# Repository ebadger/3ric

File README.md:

<h1 align="center">3ric</h1>

<p align="center">
  <strong>A from-scratch, Apple-II-class 65C02 personal computer — real hardware plus a
  cycle-honest emulator that also runs in your browser.</strong>
</p>

<p align="center">

</p>

---

## ▶ Try it now — no install, no account

**[Built from Bits: the Hackaday showcase](https://ebadger.github.io/3ric/hackaday.html)**
is a one-minute tour of the machine: a hi-res starfield, 16-color plasma, a rotating
wireframe, and an original six-voice stereo chiptune, all running as real 65C02 code.
[Run and remix the demo](https://ebadger.github.io/3ric/index.html?src=programs/hackaday.s)
at **1x**, then click the emulator for sound. Use **1-4** for scenes, **Space** to pause,
**M** to mute, and **Q/Esc** to return to the monitor. Source and `.PRG` / `.woz`
exports are available in the editor; the program targets 3RIC, not an unmodified Apple II.

**<https://ebadger.github.io/3ric/>** runs the *entire machine* client-side via
WebAssembly. Click the canvas and start typing at the DOS `>` prompt (`MON` enters the
monitor's `*` prompt). Then:

- **Boot Disk** — boot the demo 5.25″ floppy (a self-booting machine-code disk).
- **Mount SD** — mount the micro-SD card and use the ROM's DOS shell (`DIR`, etc.).
- **Play Dirt Bike** — [ebadger.github.io/3ric/?brun=DIRTBIKE/DIRTBIKE.PRG](https://ebadger.github.io/3ric/?brun=DIRTBIKE/DIRTBIKE.PRG)
  boots Arnaud Verhille's Apple II motocross from the SD card through the ROM DOS
  (`CD DIRTBIKE`, `BRUN DIRTBIKE.PRG 0800`). It takes about 10 seconds to load; play
  with the keyboard or a gamepad.
- **Assemble & Run** — open the built-in 65C02 editor, write assembly, and run it like
  `BRUN` — all in the browser. Programs are shareable via a `?src=` deep link.

<!-- TODO(media): drop an animated GIF of the emulator booting + a program running here,
     e.g. . Keep it < ~5 MB for fast README loads. -->

## What is 3ric?

3ric is a personal *learn-by-building* project: an 8-bit computer designed at the chip level
— KiCad schematics, a custom PCB, and 74-series address-decode logic — paired with a C++
emulator of the exact same machine. The emulator compiles to WebAssembly, so the **same VM
core** that models the real hardware also boots the unmodified 512 KB ROM in any browser.
The whole journey is documented in a [YouTube build series][youtube].

> **Why it exists:** to understand, build, document, and demonstrate how an Apple-II-class
> computer works end to end — and to let anyone poke at it with zero friction. See
> [`docs/MISSION.md`](docs/MISSION.md).

## Features

- **65C02 CPU** with a faithful memory map and soft switches, adjustable clock speed.
- **Video**: 40×24 text, lo-res, and hi-res color, rendered to a canvas.
- **Input & I/O**: keyboard (`$C000`/`$C010`), 6551-style ACIA serial, 6522 VIA.
- **Disk II 5.25″ floppy** via `.woz` images (self-booting machine-code disks).
- **Micro-SD storage**: a bit-banged SPI FAT32 card with a ROM DOS shell.
- **In-browser 65C02 assembler/editor** — assemble & run, download a `.PRG`, share `?src=`
  links; ships ~11 sample programs.
- **AI-generated 6502 games** (STAR DUEL, Snake, Life, Minesweeper, 2048, Star Swarm, and more) built
  through the project's own codegen pipeline — see [`emulator/AICodeGen/`](emulator/AICodeGen/).
- **Runs everywhere the same way**: one shared C++ VM core drives both the native Windows
  build and the browser (WebAssembly) build.

## Write your first program in the browser

1. Open the [live emulator][demo] and pick a sample from the editor's program menu.
2. Edit the assembly, hit **Assemble & Run**, and watch it execute on the machine.
3. Use **Download .PRG** to save it, or copy the `?src=` link to share the exact program.

Prebuilt samples live in [`web/programs/`](web/programs/); their source and design notes
are under [`emulator/AICodeGen/`](emulator/AICodeGen/) and [`codegen/`](codegen/).

## Build from source

Full, current instructions are in [`status/SYSTEM-STATUS.md`](status/SYSTEM-STATUS.md).

**Native emulator (Windows):** open `emulator/Badger6502VM.sln` in Visual Studio 2022 and
build/run the `Console` or WinUI (`Badger6502Emulator`) host.

**Browser / WebAssembly build** (emsdk 6.0.1, Node, Python 3):

```powershell
pwsh web/build.ps1     # Emscripten -> web/badger6502.js + .wasm, stages data/
pwsh web/serve.ps1     # serves http://localhost:8011/index.html
```

**Verify it's healthy** (headless smoke tests — no WASM build needed for the first one):

```powershell
$node = "C:\Users\ebadger\emsdk\node\22.16.0_64bit\bin\node.exe"
& $node codegen/tools/asm6502.test.mjs   # assembler encoding tests
& $node web/test_boot.cjs                # ROM boots to a sane state
```

## How it works

```mermaid
flowchart TD
    ROM["6502 ROM + software<br/>(badger6502.bin, fontrom.dat, .s / .prg)"]
    VM["Emulator core — 65C02 VM in C++<br/>(WozLib floppy · MockMicroSD · video/keyboard/ACIA/VIA)"]
    NATIVE["Native hosts<br/>(Windows / Console)"]
    WASM["Emscripten bridge → WebAssembly"]
    BROWSER["Browser client (index.html)<br/>→ GitHub Pages"]
    CODEGEN["Codegen<br/>(asm6502 + headless harness)"]
    HW["Hardware<br/>(KiCad · 74-series logic · logisim)"]

    ROM --> VM
    VM --> NATIVE
    VM --> WASM --> BROWSER
    CODEGEN -->|assembles & tests on the same VM| VM
    HW -. mirrors the same memory map .-> VM
```

The **memory map is a shared contract**: `emulator/Badger6502VMLib/vm.h` is mirrored by the
hardware decode schematic, the web bridge, and the codegen platform reference. The architecture and
each layer are documented in [`specs/`](specs/) — start with
[`specs/SYSTEM.md`](specs/SYSTEM.md).

## Repository layout

| Path | What's there |
|------|--------------|
| [`emulator/`](emulator/) | C++ 65C02 VM core, WozLib, MockMicroSD, native hosts, ROM data, AI codegen programs |
| [`web/`](web/) | Emscripten bridge, browser client, in-browser assembler, Pages build/deploy |
| [`codegen/`](codegen/) | `asm6502` assembler, `run6502`/harness, platform-ref generation |
| [`specs/`](specs/) | Layer specifications (the source of truth — specs before code) |
| [`status/`](status/) | How to build/run/verify; current state and known gaps |
| [`docs/`](docs/) | Mission, workflow rules & learnings, roles |
| [`kicad/`](kicad/), [`logisim/`](logisim/), [`diylayout/`](diylayout/), [`schematic_pdf/`](schematic_pdf/) | Hardware: schematics, PCB, 74-series address decode, digital-logic models |
| [`22v10/`](22v10/) | Historical intermediate GAL experiments; replaced by 74-series logic in the final build |
| [`romgen/`](romgen/), [`scripts/`](scripts/), [`test/`](test/) | ROM assembly tooling, dev/CI scripts, tests |

## Known gaps

- **DOS 3.3 / Applesoft disks don't run.** This clone's `$E000` BASIC is generic Microsoft
  BASIC, not Applesoft, so games that chain through an Applesoft auto-run greeting won't
  boot. Self-booting machine-code disks work.

## Contributing

Contributions and experiments are welcome — especially new 6502 programs for the gallery.

**Add a program (the easy path).** No C++, no local build: have an AI coding tool write a
65C02 program by pointing it at [`llms.txt`](https://ebadger.github.io/3ric/llms.txt), test it
in the [browser editor][demo], and open a one-file pull request to the
[Community Gallery](https://ebadger.github.io/3ric/gallery.html). Step-by-step, with a
copy-paste prompt: **[`CONTRIBUTING.md`](CONTRIBUTING.md)**.

**Change the machine itself.** A few house rules keep it trustworthy:

- **Specs before code.** Update the relevant spec in [`specs/`](specs/) in the same change.
- **Trace every layer** a change touches (ROM/software → C++ VM core → web bridge/WASM), and
  keep the **native and browser builds behavior-identical**.
- **Open a PR** — changes land via pull request, not direct pushes to `main`.

The full workflow rules live in [`docs/LEARNINGS.md`](docs/LEARNINGS.md); bug reports use the
templates under [`.github/ISSUE_TEMPLATE/`](.github/ISSUE_TEMPLATE/).

## The build series

3ric is built in public. Watch the design and construction, episode by episode:
**[YouTube build series][youtube]**.

The [porting logs](docs/porting-logs/README.md) tell the software side of that story:
A2Robots, Spy vs Spy, Spy Hunter, and Pitfall II, with the changes, failed experiments,
hardware evidence, and lessons for future sessions.

## Support

If this project helps you learn or you just enjoy the build, please consider
**[sponsoring it on GitHub][sponsor]** — or use the **Sponsor** button at the top of this
repository (see [`.github/FUNDING.yml`](.github/FUNDING.yml)). Sponsorship funds parts,
boards, and more build videos, and **every sponsor is credited in
[`BACKERS.md`](BACKERS.md)**.

## License

3ric is **dual-licensed**:

- **Software** — [MIT](LICENSE).
- **Hardware designs & documentation** — [Creative Commons Attribution-ShareAlike 4.0
  International](LICENSE-CC-BY-SA-4.0.txt).

Bundled third-party components keep their own licenses, and some bundled data (the ROM's
Microsoft BASIC, Apple II disk images used as test fixtures) is third-party copyrighted
material **not** licensed by this project. The emulators' micro-SD card holds **Dirt Bike**,
a separate game under the GNU GPL v3, modified for 3RIC (see
[`emulator/Data/sd-card/`](emulator/Data/sd-card/README.md)). See [`NOTICE`](NOTICE) for the
full breakdown before redistributing.

[demo]: https://ebadger.github.io/3ric/
[youtube]: https://www.youtube.com/playlist?list=PLbYLt1iawSBLK4w46Kn7cxxuoeVt7Zepq
[sponsor]: https://github.com/sponsors/ebadger

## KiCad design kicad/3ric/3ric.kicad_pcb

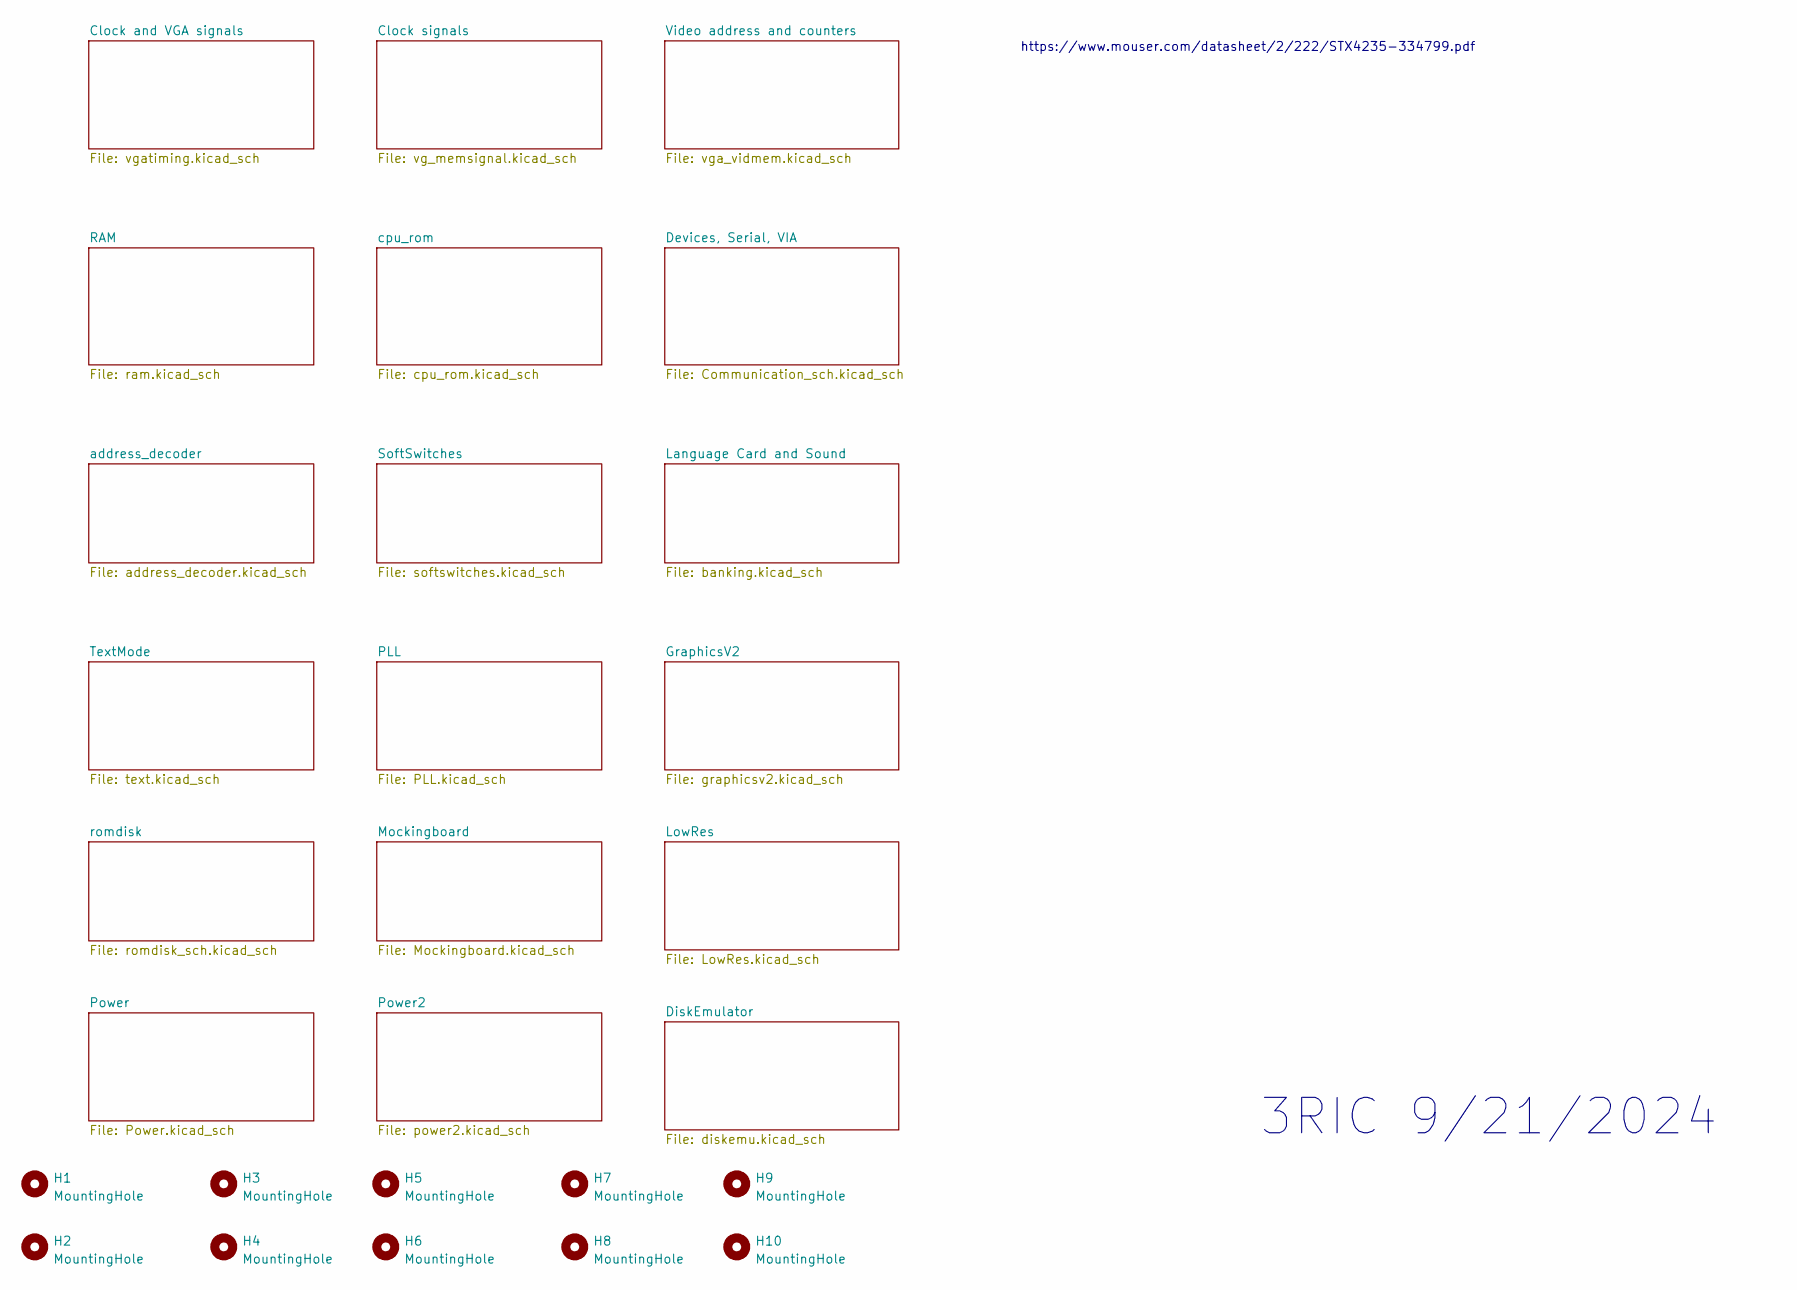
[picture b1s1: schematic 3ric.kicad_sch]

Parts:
H1, H2, H3, H4, H5, H6, H7, H8, H9, H10: MountingHole; MountingHole_4.3mm_M4

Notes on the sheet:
3RIC 9/21/2024
https://www.mouser.com/datasheet/2/222/STX4235-334799.pdf

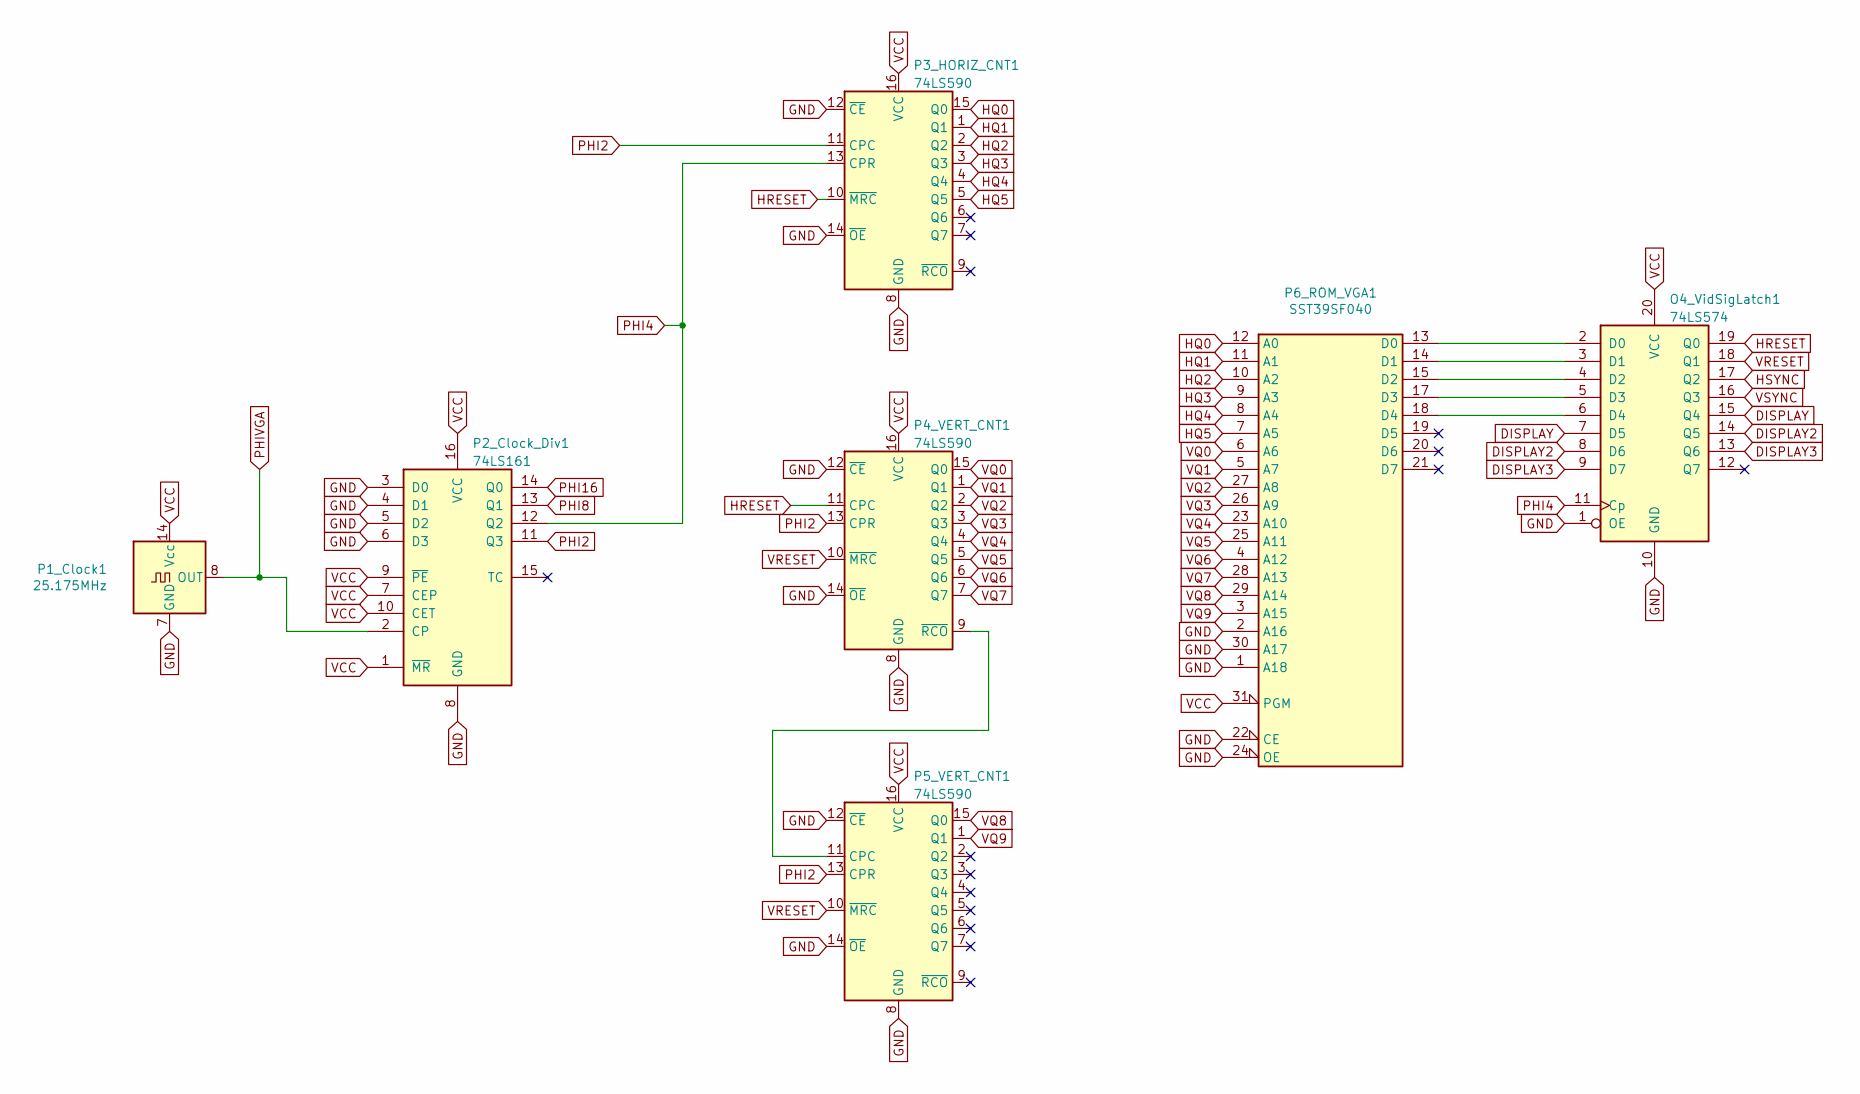
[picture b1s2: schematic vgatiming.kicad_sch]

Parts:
O4_VidSigLatch1: 74LS574; DIP-20_W7.62mm_Socket
P1_Clock1: 25.175MHz; Oscillator_DIP-14
P2_Clock_Div1: 74LS161; DIP-16_W7.62mm_Socket
P3_HORIZ_CNT1, P4_VERT_CNT1, P5_VERT_CNT1: 74LS590; DIP-16_W7.62mm_Socket
P6_ROM_VGA1: SST39SF040; DIP-32_W15.24mm_Socket

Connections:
DISPLAY: O4_VidSigLatch1.7 (D5), O4_VidSigLatch1.15 (Q4); also elsewhere on the board
DISPLAY2: O4_VidSigLatch1.8 (D6), O4_VidSigLatch1.14 (Q5); also elsewhere on the board
DISPLAY3: O4_VidSigLatch1.9 (D7), O4_VidSigLatch1.13 (Q6); also elsewhere on the board
GND: O4_VidSigLatch1.1 (OE), O4_VidSigLatch1.10 (GND), P1_Clock1.7 (GND), P2_Clock_Div1.3 (D0), P2_Clock_Div1.4 (D1), P2_Clock_Div1.5 (D2), P2_Clock_Div1.6 (D3), P2_Clock_Div1.8 (GND), P3_HORIZ_CNT1.8 (GND), P3_HORIZ_CNT1.12 (~CE), P3_HORIZ_CNT1.14 (~OE), P4_VERT_CNT1.8 (GND), P4_VERT_CNT1.12 (~CE), P4_VERT_CNT1.14 (~OE), P5_VERT_CNT1.8 (GND), P5_VERT_CNT1.12 (~CE), P5_VERT_CNT1.14 (~OE), P6_ROM_VGA1.1 (A18), P6_ROM_VGA1.2 (A16), P6_ROM_VGA1.16 (GND), P6_ROM_VGA1.22 (CE), P6_ROM_VGA1.24 (OE), P6_ROM_VGA1.30 (A17); also elsewhere on the board
HQ0: P3_HORIZ_CNT1.15 (Q0), P6_ROM_VGA1.12 (A0)
HQ1: P3_HORIZ_CNT1.1 (Q1), P6_ROM_VGA1.11 (A1)
HQ2: P3_HORIZ_CNT1.2 (Q2), P6_ROM_VGA1.10 (A2)
HQ3: P3_HORIZ_CNT1.3 (Q3), P6_ROM_VGA1.9 (A3)
HQ4: P3_HORIZ_CNT1.4 (Q4), P6_ROM_VGA1.8 (A4)
HQ5: P3_HORIZ_CNT1.5 (Q5), P6_ROM_VGA1.7 (A5)
HRESET: O4_VidSigLatch1.19 (Q0), P3_HORIZ_CNT1.10 (~MRC), P4_VERT_CNT1.11 (CPC)
HSYNC: O4_VidSigLatch1.17 (Q2); also elsewhere on the board
unnamed: O4_VidSigLatch1.2 (D0), P6_ROM_VGA1.13 (D0)
unnamed: O4_VidSigLatch1.3 (D1), P6_ROM_VGA1.14 (D1)
unnamed: O4_VidSigLatch1.4 (D2), P6_ROM_VGA1.15 (D2)
unnamed: O4_VidSigLatch1.5 (D3), P6_ROM_VGA1.17 (D3)
unnamed: O4_VidSigLatch1.6 (D4), P6_ROM_VGA1.18 (D4)
unnamed: P4_VERT_CNT1.9 (~RCO), P5_VERT_CNT1.11 (CPC)
PHI2: P2_Clock_Div1.11 (Q3), P3_HORIZ_CNT1.11 (CPC), P4_VERT_CNT1.13 (CPR), P5_VERT_CNT1.13 (CPR); also elsewhere on the board
PHI4: O4_VidSigLatch1.11 (Cp), P2_Clock_Div1.12 (Q2), P3_HORIZ_CNT1.13 (CPR); also elsewhere on the board
PHI8: P2_Clock_Div1.13 (Q1); also elsewhere on the board
PHI16: P2_Clock_Div1.14 (Q0); also elsewhere on the board
PHIVGA: P1_Clock1.8 (OUT), P2_Clock_Div1.2 (CP)
VCC: O4_VidSigLatch1.20 (VCC), P1_Clock1.14 (Vcc), P2_Clock_Div1.1 (~MR), P2_Clock_Div1.7 (CEP), P2_Clock_Div1.9 (~PE), P2_Clock_Div1.10 (CET), P2_Clock_Div1.16 (VCC), P3_HORIZ_CNT1.16 (VCC), P4_VERT_CNT1.16 (VCC), P5_VERT_CNT1.16 (VCC), P6_ROM_VGA1.31 (PGM), P6_ROM_VGA1.32 (VCC); also elsewhere on the board
VQ0: P4_VERT_CNT1.15 (Q0), P6_ROM_VGA1.6 (A6); also elsewhere on the board
VQ1: P4_VERT_CNT1.1 (Q1), P6_ROM_VGA1.5 (A7); also elsewhere on the board
VQ2: P4_VERT_CNT1.2 (Q2), P6_ROM_VGA1.27 (A8); also elsewhere on the board
VQ3: P4_VERT_CNT1.3 (Q3), P6_ROM_VGA1.26 (A9); also elsewhere on the board
VQ4: P4_VERT_CNT1.4 (Q4), P6_ROM_VGA1.23 (A10); also elsewhere on the board
VQ5: P4_VERT_CNT1.5 (Q5), P6_ROM_VGA1.25 (A11); also elsewhere on the board
VQ6: P4_VERT_CNT1.6 (Q6), P6_ROM_VGA1.4 (A12); also elsewhere on the board
VQ7: P4_VERT_CNT1.7 (Q7), P6_ROM_VGA1.28 (A13); also elsewhere on the board
VQ8: P5_VERT_CNT1.15 (Q0), P6_ROM_VGA1.29 (A14); also elsewhere on the board
VQ9: P5_VERT_CNT1.1 (Q1), P6_ROM_VGA1.3 (A15)
VRESET: O4_VidSigLatch1.18 (Q1), P4_VERT_CNT1.10 (~MRC), P5_VERT_CNT1.10 (~MRC)
VSYNC: O4_VidSigLatch1.16 (Q3); also elsewhere on the board

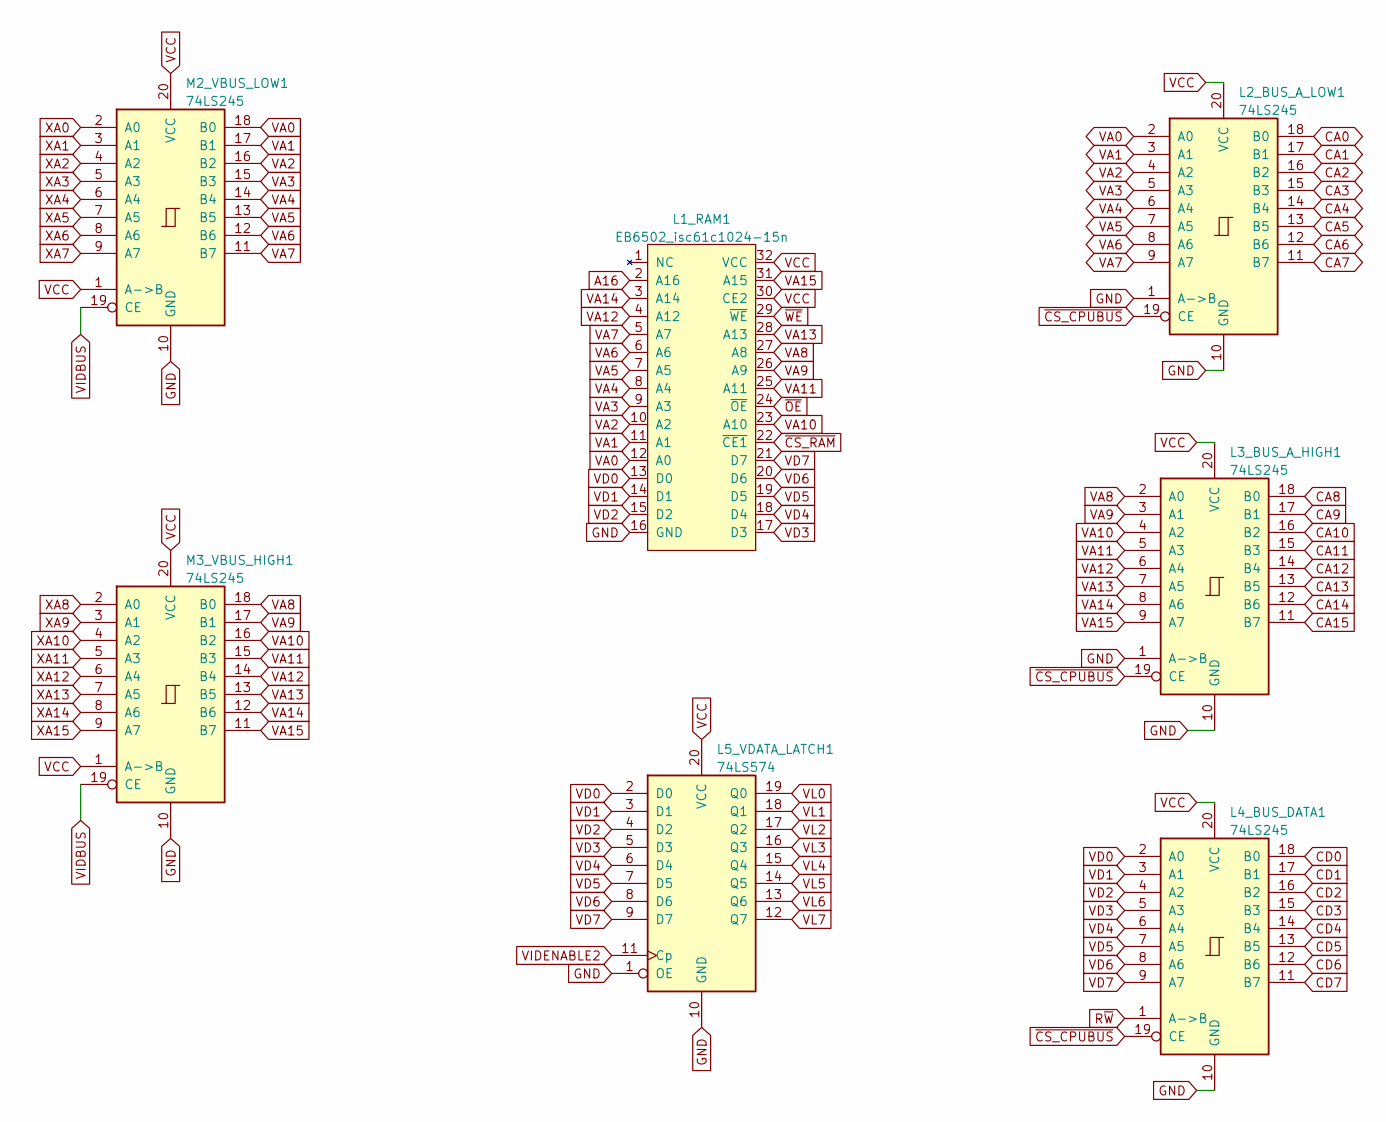
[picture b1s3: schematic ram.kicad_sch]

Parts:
L1_RAM1: EB6502_isc61c1024-15n; DIP-32_W7.62mm
L2_BUS_A_LOW1, L3_BUS_A_HIGH1, L4_BUS_DATA1: 74LS245; DIP-20_W7.62mm_Socket
L5_VDATA_LATCH1: 74LS574; DIP-20_W7.62mm_Socket
M2_VBUS_LOW1, M3_VBUS_HIGH1: 74LS245; DIP-20_W7.62mm_Socket

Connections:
A16: L1_RAM1.2 (A16); also elsewhere on the board
CA0: L2_BUS_A_LOW1.18 (B0); also elsewhere on the board
CA1: L2_BUS_A_LOW1.17 (B1); also elsewhere on the board
CA2: L2_BUS_A_LOW1.16 (B2); also elsewhere on the board
CA3: L2_BUS_A_LOW1.15 (B3); also elsewhere on the board
CA4: L2_BUS_A_LOW1.14 (B4); also elsewhere on the board
CA5: L2_BUS_A_LOW1.13 (B5); also elsewhere on the board
CA6: L2_BUS_A_LOW1.12 (B6); also elsewhere on the board
CA7: L2_BUS_A_LOW1.11 (B7); also elsewhere on the board
CA8: L3_BUS_A_HIGH1.18 (B0); also elsewhere on the board
CA9: L3_BUS_A_HIGH1.17 (B1); also elsewhere on the board
CA10: L3_BUS_A_HIGH1.16 (B2); also elsewhere on the board
CA11: L3_BUS_A_HIGH1.15 (B3); also elsewhere on the board
CA12: L3_BUS_A_HIGH1.14 (B4); also elsewhere on the board
CA13: L3_BUS_A_HIGH1.13 (B5); also elsewhere on the board
CA14: L3_BUS_A_HIGH1.12 (B6); also elsewhere on the board
CA15: L3_BUS_A_HIGH1.11 (B7); also elsewhere on the board
CD0: L4_BUS_DATA1.18 (B0); also elsewhere on the board
CD1: L4_BUS_DATA1.17 (B1); also elsewhere on the board
CD2: L4_BUS_DATA1.16 (B2); also elsewhere on the board
CD3: L4_BUS_DATA1.15 (B3); also elsewhere on the board
CD4: L4_BUS_DATA1.14 (B4); also elsewhere on the board
CD5: L4_BUS_DATA1.13 (B5); also elsewhere on the board
CD6: L4_BUS_DATA1.12 (B6); also elsewhere on the board
CD7: L4_BUS_DATA1.11 (B7); also elsewhere on the board
GND: L1_RAM1.16 (GND), L2_BUS_A_LOW1.1 (A->B), L2_BUS_A_LOW1.10 (GND), L3_BUS_A_HIGH1.1 (A->B), L3_BUS_A_HIGH1.10 (GND), L4_BUS_DATA1.10 (GND), L5_VDATA_LATCH1.1 (OE), L5_VDATA_LATCH1.10 (GND), M2_VBUS_LOW1.10 (GND), M3_VBUS_HIGH1.10 (GND); also elsewhere on the board
R~W: L4_BUS_DATA1.1 (A->B); also elsewhere on the board
VA0: L1_RAM1.12 (A0), L2_BUS_A_LOW1.2 (A0), M2_VBUS_LOW1.18 (B0)
VA1: L1_RAM1.11 (A1), L2_BUS_A_LOW1.3 (A1), M2_VBUS_LOW1.17 (B1)
VA2: L1_RAM1.10 (A2), L2_BUS_A_LOW1.4 (A2), M2_VBUS_LOW1.16 (B2)
VA3: L1_RAM1.9 (A3), L2_BUS_A_LOW1.5 (A3), M2_VBUS_LOW1.15 (B3)
VA4: L1_RAM1.8 (A4), L2_BUS_A_LOW1.6 (A4), M2_VBUS_LOW1.14 (B4)
VA5: L1_RAM1.7 (A5), L2_BUS_A_LOW1.7 (A5), M2_VBUS_LOW1.13 (B5)
VA6: L1_RAM1.6 (A6), L2_BUS_A_LOW1.8 (A6), M2_VBUS_LOW1.12 (B6)
VA7: L1_RAM1.5 (A7), L2_BUS_A_LOW1.9 (A7), M2_VBUS_LOW1.11 (B7)
VA8: L1_RAM1.27 (A8), L3_BUS_A_HIGH1.2 (A0), M3_VBUS_HIGH1.18 (B0)
VA9: L1_RAM1.26 (A9), L3_BUS_A_HIGH1.3 (A1), M3_VBUS_HIGH1.17 (B1)
VA10: L1_RAM1.23 (A10), L3_BUS_A_HIGH1.4 (A2), M3_VBUS_HIGH1.16 (B2)
VA11: L1_RAM1.25 (A11), L3_BUS_A_HIGH1.5 (A3), M3_VBUS_HIGH1.15 (B3)
VA12: L1_RAM1.4 (A12), L3_BUS_A_HIGH1.6 (A4), M3_VBUS_HIGH1.14 (B4)
VA13: L1_RAM1.28 (A13), L3_BUS_A_HIGH1.7 (A5), M3_VBUS_HIGH1.13 (B5)
VA14: L1_RAM1.3 (A14), L3_BUS_A_HIGH1.8 (A6), M3_VBUS_HIGH1.12 (B6)
VA15: L1_RAM1.31 (A15), L3_BUS_A_HIGH1.9 (A7), M3_VBUS_HIGH1.11 (B7)
VCC: L1_RAM1.30 (CE2), L1_RAM1.32 (VCC), L2_BUS_A_LOW1.20 (VCC), L3_BUS_A_HIGH1.20 (VCC), L4_BUS_DATA1.20 (VCC), L5_VDATA_LATCH1.20 (VCC), M2_VBUS_LOW1.1 (A->B), M2_VBUS_LOW1.20 (VCC), M3_VBUS_HIGH1.1 (A->B), M3_VBUS_HIGH1.20 (VCC); also elsewhere on the board
VD0: L1_RAM1.13 (D0), L4_BUS_DATA1.2 (A0), L5_VDATA_LATCH1.2 (D0)
VD1: L1_RAM1.14 (D1), L4_BUS_DATA1.3 (A1), L5_VDATA_LATCH1.3 (D1)
VD2: L1_RAM1.15 (D2), L4_BUS_DATA1.4 (A2), L5_VDATA_LATCH1.4 (D2)
VD3: L1_RAM1.17 (D3), L4_BUS_DATA1.5 (A3), L5_VDATA_LATCH1.5 (D3)
VD4: L1_RAM1.18 (D4), L4_BUS_DATA1.6 (A4), L5_VDATA_LATCH1.6 (D4)
VD5: L1_RAM1.19 (D5), L4_BUS_DATA1.7 (A5), L5_VDATA_LATCH1.7 (D5)
VD6: L1_RAM1.20 (D6), L4_BUS_DATA1.8 (A6), L5_VDATA_LATCH1.8 (D6)
VD7: L1_RAM1.21 (D7), L4_BUS_DATA1.9 (A7), L5_VDATA_LATCH1.9 (D7)
VIDBUS: M2_VBUS_LOW1.19 (CE), M3_VBUS_HIGH1.19 (CE); also elsewhere on the board
VIDENABLE2: L5_VDATA_LATCH1.11 (Cp); also elsewhere on the board
VL0: L5_VDATA_LATCH1.19 (Q0); also elsewhere on the board
VL1: L5_VDATA_LATCH1.18 (Q1); also elsewhere on the board
VL2: L5_VDATA_LATCH1.17 (Q2); also elsewhere on the board
VL3: L5_VDATA_LATCH1.16 (Q3); also elsewhere on the board
VL4: L5_VDATA_LATCH1.15 (Q4); also elsewhere on the board
VL5: L5_VDATA_LATCH1.14 (Q5); also elsewhere on the board
VL6: L5_VDATA_LATCH1.13 (Q6); also elsewhere on the board
VL7: L5_VDATA_LATCH1.12 (Q7); also elsewhere on the board
XA0: M2_VBUS_LOW1.2 (A0); also elsewhere on the board
XA1: M2_VBUS_LOW1.3 (A1); also elsewhere on the board
XA2: M2_VBUS_LOW1.4 (A2); also elsewhere on the board
XA3: M2_VBUS_LOW1.5 (A3); also elsewhere on the board
XA4: M2_VBUS_LOW1.6 (A4); also elsewhere on the board
XA5: M2_VBUS_LOW1.7 (A5); also elsewhere on the board
XA6: M2_VBUS_LOW1.8 (A6); also elsewhere on the board
XA7: M2_VBUS_LOW1.9 (A7); also elsewhere on the board
XA8: M3_VBUS_HIGH1.2 (A0); also elsewhere on the board
XA9: M3_VBUS_HIGH1.3 (A1); also elsewhere on the board
XA10: M3_VBUS_HIGH1.4 (A2); also elsewhere on the board
XA11: M3_VBUS_HIGH1.5 (A3); also elsewhere on the board
XA12: M3_VBUS_HIGH1.6 (A4); also elsewhere on the board
XA13: M3_VBUS_HIGH1.7 (A5); also elsewhere on the board
XA14: M3_VBUS_HIGH1.8 (A6); also elsewhere on the board
XA15: M3_VBUS_HIGH1.9 (A7); also elsewhere on the board
~CS_CPUBUS: L2_BUS_A_LOW1.19 (CE), L3_BUS_A_HIGH1.19 (CE), L4_BUS_DATA1.19 (CE); also elsewhere on the board
~CS_RAM: L1_RAM1.22 (~CE1); also elsewhere on the board
~OE: L1_RAM1.24 (~OE); also elsewhere on the board
~WE: L1_RAM1.29 (~WE); also elsewhere on the board

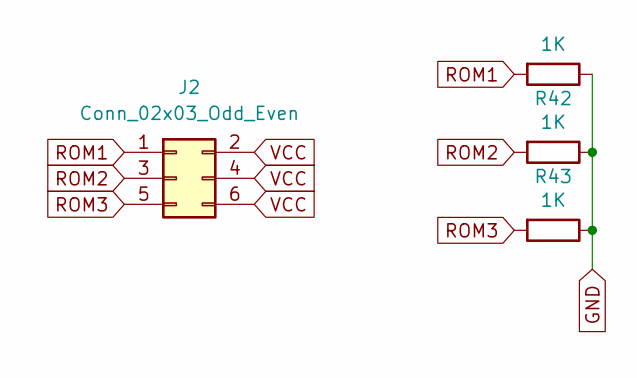
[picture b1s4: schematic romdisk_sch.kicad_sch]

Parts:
J2: Conn_02x03_Odd_Even; PinHeader_2x03_P2.54mm_Vertical
R41, R42, R43: 1K; R_0402_1005Metric_Pad0.72x0.64mm_HandSolder

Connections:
GND: R41.1, R42.1, R43.1; also elsewhere on the board
ROM1: J2.1, R41.2; also elsewhere on the board
ROM2: J2.3, R42.2; also elsewhere on the board
ROM3: J2.5, R43.2; also elsewhere on the board
VCC: J2.2, J2.4, J2.6; also elsewhere on the board

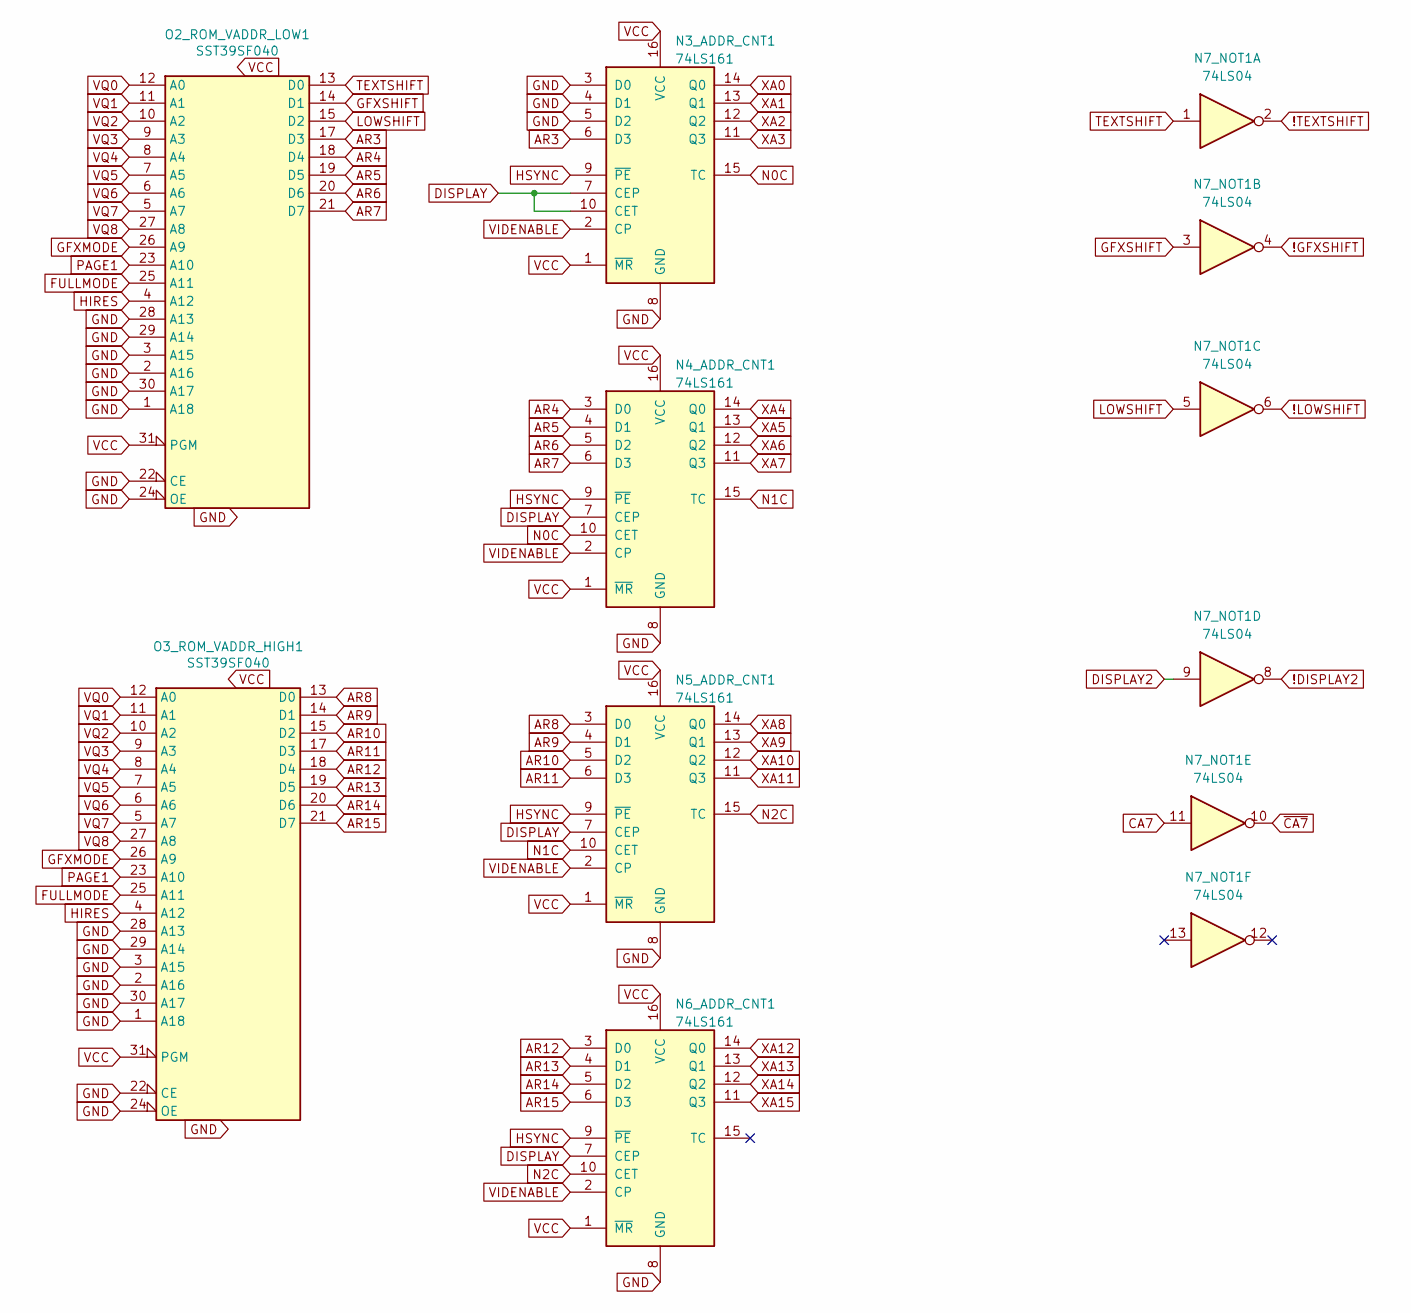
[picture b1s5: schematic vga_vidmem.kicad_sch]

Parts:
N3_ADDR_CNT1, N4_ADDR_CNT1, N5_ADDR_CNT1, N6_ADDR_CNT1: 74LS161; DIP-16_W7.62mm_Socket
N7_NOT1: 74LS04; DIP-14_W7.62mm_Socket
O2_ROM_VADDR_LOW1, O3_ROM_VADDR_HIGH1: SST39SF040; DIP-32_W15.24mm_Socket

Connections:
!DISPLAY2: N7_NOT1.8; also elsewhere on the board
!GFXSHIFT: N7_NOT1.4; also elsewhere on the board
!LOWSHIFT: N7_NOT1.6; also elsewhere on the board
!TEXTSHIFT: N7_NOT1.2; also elsewhere on the board
AR3: N3_ADDR_CNT1.6 (D3), O2_ROM_VADDR_LOW1.17 (D3)
AR4: N4_ADDR_CNT1.3 (D0), O2_ROM_VADDR_LOW1.18 (D4)
AR5: N4_ADDR_CNT1.4 (D1), O2_ROM_VADDR_LOW1.19 (D5)
AR6: N4_ADDR_CNT1.5 (D2), O2_ROM_VADDR_LOW1.20 (D6)
AR7: N4_ADDR_CNT1.6 (D3), O2_ROM_VADDR_LOW1.21 (D7)
AR8: N5_ADDR_CNT1.3 (D0), O3_ROM_VADDR_HIGH1.13 (D0)
AR9: N5_ADDR_CNT1.4 (D1), O3_ROM_VADDR_HIGH1.14 (D1)
AR10: N5_ADDR_CNT1.5 (D2), O3_ROM_VADDR_HIGH1.15 (D2)
AR11: N5_ADDR_CNT1.6 (D3), O3_ROM_VADDR_HIGH1.17 (D3)
AR12: N6_ADDR_CNT1.3 (D0), O3_ROM_VADDR_HIGH1.18 (D4)
AR13: N6_ADDR_CNT1.4 (D1), O3_ROM_VADDR_HIGH1.19 (D5)
AR14: N6_ADDR_CNT1.5 (D2), O3_ROM_VADDR_HIGH1.20 (D6)
AR15: N6_ADDR_CNT1.6 (D3), O3_ROM_VADDR_HIGH1.21 (D7)
CA7: N7_NOT1.11; also elsewhere on the board
DISPLAY: N3_ADDR_CNT1.7 (CEP), N3_ADDR_CNT1.10 (CET), N4_ADDR_CNT1.7 (CEP), N5_ADDR_CNT1.7 (CEP), N6_ADDR_CNT1.7 (CEP); also elsewhere on the board
DISPLAY2: N7_NOT1.9; also elsewhere on the board
FULLMODE: O2_ROM_VADDR_LOW1.25 (A11), O3_ROM_VADDR_HIGH1.25 (A11); also elsewhere on the board
GFXMODE: O2_ROM_VADDR_LOW1.26 (A9), O3_ROM_VADDR_HIGH1.26 (A9); also elsewhere on the board
GFXSHIFT: N7_NOT1.3, O2_ROM_VADDR_LOW1.14 (D1)
GND: N3_ADDR_CNT1.3 (D0), N3_ADDR_CNT1.4 (D1), N3_ADDR_CNT1.5 (D2), N3_ADDR_CNT1.8 (GND), N4_ADDR_CNT1.8 (GND), N5_ADDR_CNT1.8 (GND), N6_ADDR_CNT1.8 (GND), O2_ROM_VADDR_LOW1.1 (A18), O2_ROM_VADDR_LOW1.2 (A16), O2_ROM_VADDR_LOW1.3 (A15), O2_ROM_VADDR_LOW1.16 (GND), O2_ROM_VADDR_LOW1.22 (CE), O2_ROM_VADDR_LOW1.24 (OE), O2_ROM_VADDR_LOW1.28 (A13), O2_ROM_VADDR_LOW1.29 (A14), O2_ROM_VADDR_LOW1.30 (A17), O3_ROM_VADDR_HIGH1.1 (A18), O3_ROM_VADDR_HIGH1.2 (A16), O3_ROM_VADDR_HIGH1.3 (A15), O3_ROM_VADDR_HIGH1.16 (GND), O3_ROM_VADDR_HIGH1.22 (CE), O3_ROM_VADDR_HIGH1.24 (OE), O3_ROM_VADDR_HIGH1.28 (A13), O3_ROM_VADDR_HIGH1.29 (A14), O3_ROM_VADDR_HIGH1.30 (A17); also elsewhere on the board
HIRES: O2_ROM_VADDR_LOW1.4 (A12), O3_ROM_VADDR_HIGH1.4 (A12); also elsewhere on the board
HSYNC: N3_ADDR_CNT1.9 (~PE), N4_ADDR_CNT1.9 (~PE), N5_ADDR_CNT1.9 (~PE), N6_ADDR_CNT1.9 (~PE); also elsewhere on the board
LOWSHIFT: N7_NOT1.5, O2_ROM_VADDR_LOW1.15 (D2); also elsewhere on the board
N0C: N3_ADDR_CNT1.15 (TC), N4_ADDR_CNT1.10 (CET)
N1C: N4_ADDR_CNT1.15 (TC), N5_ADDR_CNT1.10 (CET)
N2C: N5_ADDR_CNT1.15 (TC), N6_ADDR_CNT1.10 (CET)
PAGE1: O2_ROM_VADDR_LOW1.23 (A10), O3_ROM_VADDR_HIGH1.23 (A10); also elsewhere on the board
TEXTSHIFT: N7_NOT1.1, O2_ROM_VADDR_LOW1.13 (D0); also elsewhere on the board
VCC: N3_ADDR_CNT1.1 (~MR), N3_ADDR_CNT1.16 (VCC), N4_ADDR_CNT1.1 (~MR), N4_ADDR_CNT1.16 (VCC), N5_ADDR_CNT1.1 (~MR), N5_ADDR_CNT1.16 (VCC), N6_ADDR_CNT1.1 (~MR), N6_ADDR_CNT1.16 (VCC), O2_ROM_VADDR_LOW1.31 (PGM), O2_ROM_VADDR_LOW1.32 (VCC), O3_ROM_VADDR_HIGH1.31 (PGM), O3_ROM_VADDR_HIGH1.32 (VCC); also elsewhere on the board
VIDENABLE: N3_ADDR_CNT1.2 (CP), N4_ADDR_CNT1.2 (CP), N5_ADDR_CNT1.2 (CP), N6_ADDR_CNT1.2 (CP); also elsewhere on the board
VQ0: O2_ROM_VADDR_LOW1.12 (A0), O3_ROM_VADDR_HIGH1.12 (A0); also elsewhere on the board
VQ1: O2_ROM_VADDR_LOW1.11 (A1), O3_ROM_VADDR_HIGH1.11 (A1); also elsewhere on the board
VQ2: O2_ROM_VADDR_LOW1.10 (A2), O3_ROM_VADDR_HIGH1.10 (A2); also elsewhere on the board
VQ3: O2_ROM_VADDR_LOW1.9 (A3), O3_ROM_VADDR_HIGH1.9 (A3); also elsewhere on the board
VQ4: O2_ROM_VADDR_LOW1.8 (A4), O3_ROM_VADDR_HIGH1.8 (A4); also elsewhere on the board
VQ5: O2_ROM_VADDR_LOW1.7 (A5), O3_ROM_VADDR_HIGH1.7 (A5); also elsewhere on the board
VQ6: O2_ROM_VADDR_LOW1.6 (A6), O3_ROM_VADDR_HIGH1.6 (A6); also elsewhere on the board
VQ7: O2_ROM_VADDR_LOW1.5 (A7), O3_ROM_VADDR_HIGH1.5 (A7); also elsewhere on the board
VQ8: O2_ROM_VADDR_LOW1.27 (A8), O3_ROM_VADDR_HIGH1.27 (A8); also elsewhere on the board
XA0: N3_ADDR_CNT1.14 (Q0); also elsewhere on the board
XA1: N3_ADDR_CNT1.13 (Q1); also elsewhere on the board
XA2: N3_ADDR_CNT1.12 (Q2); also elsewhere on the board
XA3: N3_ADDR_CNT1.11 (Q3); also elsewhere on the board
XA4: N4_ADDR_CNT1.14 (Q0); also elsewhere on the board
XA5: N4_ADDR_CNT1.13 (Q1); also elsewhere on the board
XA6: N4_ADDR_CNT1.12 (Q2); also elsewhere on the board
XA7: N4_ADDR_CNT1.11 (Q3); also elsewhere on the board
XA8: N5_ADDR_CNT1.14 (Q0); also elsewhere on the board
XA9: N5_ADDR_CNT1.13 (Q1); also elsewhere on the board
XA10: N5_ADDR_CNT1.12 (Q2); also elsewhere on the board
XA11: N5_ADDR_CNT1.11 (Q3); also elsewhere on the board
XA12: N6_ADDR_CNT1.14 (Q0); also elsewhere on the board
XA13: N6_ADDR_CNT1.13 (Q1); also elsewhere on the board
XA14: N6_ADDR_CNT1.12 (Q2); also elsewhere on the board
XA15: N6_ADDR_CNT1.11 (Q3); also elsewhere on the board
~CA7: N7_NOT1.10; also elsewhere on the board

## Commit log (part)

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2023-08-28 3ric initial schematics commit
2023-08-28 adjustments to simplify breadboard bring up
2023-09-03 PLD used for glue logic
2023-09-03 tool to generate low and high ROMs for video addresses based on graphics mode and graphics page
2023-09-03 tool to generate ROM for video sync signals, used by video hardware to determine when to send vertical sync, horizontal sync, and when display should be enabled or not
2023-09-03 Tool to build the font ROM
2023-09-04 tweak image address generation
2023-09-09 a2color PLD video rom tweaks
2023-09-09 fix rendering edge case
2023-09-12 schematic updates - bring the schematics up to match breadboard changes current state has high res Apple II color emulation working
2023-09-12 add PDF of schematics
    schematic contains latest version of breadboard changes - still requires validation with probe against breadboard
2023-09-14 logisim decoder logic for address decoding, ram banking, rom banking
2023-09-15 test tool to validate memory map logic update the memory map logic to fix bugs
2023-09-15 update test tool to enable validation of changes
2023-09-15 implement decoding logic in PLD
2023-09-16 update test tool to generate wincupl test data update 22v10 to include a16
2023-09-16 badger6502 emulator
2023-09-16 remove ftdi references fix build errors
2023-09-17 changes to bring closer to 3ric design
2023-09-22 add SD card emulation!
    Make closer to Apple II
2023-09-25 stash latest simulation and schematic changes - adding untested soft switches and RAM banking
2023-09-29 update pdf of schematic
2023-10-08 emulator updates for 3ric
2023-10-08 updates to logisim project and schematics
2023-10-08 latest simulator changes s
2023-10-10 move some of the logic to PLD, move device range from C1XX to CX00 update device labels to be more correct update PLD
2023-10-21 update video ram generation tool to support mixed mode and low res
2023-10-22 tweak pld
2023-10-22 update pld logic
2023-11-24 update emulator to allow breaking on memory reads to break on jumps outside of a specified range
2023-11-26 add banking support to emulator
2023-12-01 SD card write emulation - improvements to debugger
2023-12-09 update breakpoint logic - update text display to better work with Apple games
2023-12-19 significant emulator threading and perf fixes
    update fontgen tool to match apple II font
2024-01-26 via timer, computer changes
2024-02-18 push schematic updates
2024-02-18 add lowres signal to sync rom
2024-03-02 support mixed mode and lores graphics
2024-03-02 add diy layout file for breadboard layout mapping added PLL breadboard
2024-03-02 latest ROM changes
2024-03-03 3 breadboards down
2024-03-09 updated breadboard
2024-03-25 update schematics
2024-03-25 update breadboard layout, started on VIA1
2024-03-30 updates to layout
2024-03-30 upgraded to kicad 8, updates to schematic - added snes controllers, mouse port, many fixes
2024-04-12 add logic to to logisim to prepare for disk access C600-C7FF reads will now select ROM C0EX triggers device 0
2024-04-13 start adding support for WOZ file format
    modifying emulator to support disk soft switches
    creating wozfile object to read a wozfile, grab the chunks.
    added a test app to validate the wozfile class
2024-04-14 Working Apple disk emulator supporting WOZ2 files. Reads only, no writing yet
2024-04-21 save the latest changes
2024-04-26 schematic updates
2024-04-26 update schematic to include disk components
2024-04-27 builing on arm64 device
2024-04-27 improve graphics rendering, use a map instead of a vector for changes and put reresh of display on a timer. 60 fps timer and coalesce the changes.
2024-04-27 some good bugfixing - made mixed mode with hires work properly. Also cleaned up the code around the graphics pages by using arrays
2024-04-27 graphics bug fixes
2024-04-27 thread safe disk
2024-04-27 dsk2woz2 converted tool to command line and updated to work with modern VS
2024-04-27 fix some shutdown crashing bugs
2024-04-28 initial apple drive emulator for my 3r1c
2024-04-28 dsk2woz2 for arm
2024-04-29 integrate consolew with pico - have SD card working, basic console commands working arduino rig for testing
2024-04-29 arduino test harness sketch
2024-04-30 integrate the arduino serial with the console on the pico. verifies the protocol with the pico for sending and receiving bytes from the console
2024-04-30 update pico to work with Arduino harness for console integration. Validates that the console device is working
2024-05-06 update console project, update picodisk after testing with arduino and oscilliscope to tweak timing for 6502
2024-05-06 updates to the arduino test harness for pico disk
2024-05-06 and it now works, both read and write
2024-05-19 actually can load drol, pf2 on 3ric
2024-05-25 add control to pause processor
2024-05-28 not working, but stashing changes
2024-05-29 working again, still drol and pf2 only efficient addcycles call at ~1.7usec
2024-05-29 stash windows emulator changes
2024-05-30 update emulator to better match the machine. udpate machine version
2024-05-31 and it works - was overflowing an int16 for file offset so file could only access track data up to 64K works now.
2024-08-10 stash picodisk changes and 3ric.diy layout
2024-08-10 stash changes
2024-09-03 update the breadboard map and the schematics
2024-09-07 wiring continued
2024-09-15 picking up steam on the layout - lots of progress
2024-09-16 update units for soft switch logic to match breadboard
2024-09-22 update schematic based on breadboard
2024-09-22 update the pdf
2024-09-22 update the date in the schematic and pdf
2024-09-23 finish 2nd set of breadboards, soft switches, signals, language board
2024-09-23 update schematic with corrections found via virutal wiring
2024-09-23 add a pdf of the breadboard layout
2024-09-28 completed? Everything wired in layout creator and first draft of completed schematic
2024-09-28 add sd card footprints
2024-09-28 cleaning up of the schematic
2024-10-01 updated schematics and PCB PNG of the breadboard layout
2024-10-08 pcb layout continued
2024-10-09 so close! PCB ready to go?
2024-10-11 stash latest rom generation changes - probably for lo res color
2024-10-13 stash latest
2024-11-16 v2 pcb
2025-02-01 tweak output for better rendering on a terminal
2025-02-01 python script to convert dos font to assembly data rotated 90 degrees for easy banner printing
2025-11-29 Add link to YouTube videos in README

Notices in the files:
README.md:
Code license: MIT
Hardware & docs: CC BY-SA 4.0
